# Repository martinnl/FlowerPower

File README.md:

FlowerPower
===========

Flower watering and nutrition controller
as

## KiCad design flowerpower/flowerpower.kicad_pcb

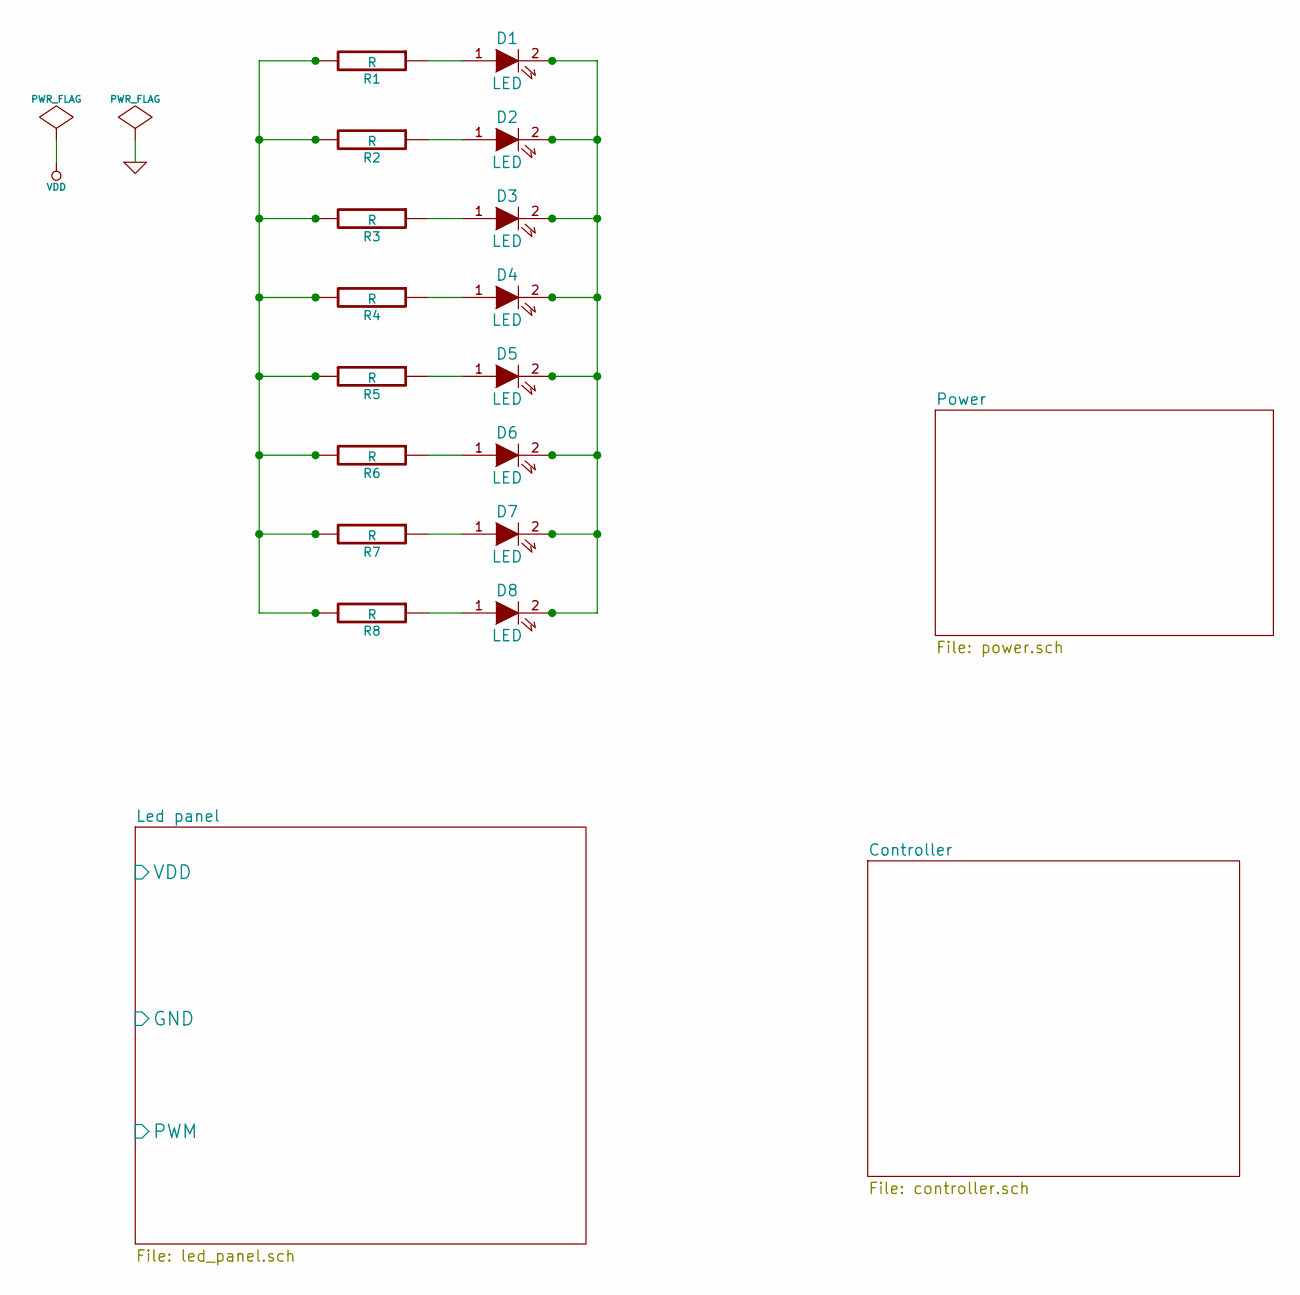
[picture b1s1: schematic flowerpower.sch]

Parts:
D1, D2, D3, D4, D5, D6, D7, D8: LED
R1, R2, R3, R4, R5, R6, R7, R8: R

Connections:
unnamed: D6.1 (A), R6.1
unnamed: D5.1 (A), R5.1
unnamed: D7.1 (A), R7.1
unnamed: D4.1 (A), R4.1
unnamed: D3.1 (A), R3.1
unnamed: R1.2, R2.2, R3.2, R4.2, R5.2, R6.2, R7.2, R8.2
unnamed: D1.2 (K), D2.2 (K), D3.2 (K), D4.2 (K), D5.2 (K), D6.2 (K), D7.2 (K), D8.2 (K)
unnamed: D8.1 (A), R8.1
unnamed: D1.1 (A), R1.1
unnamed: D2.1 (A), R2.1

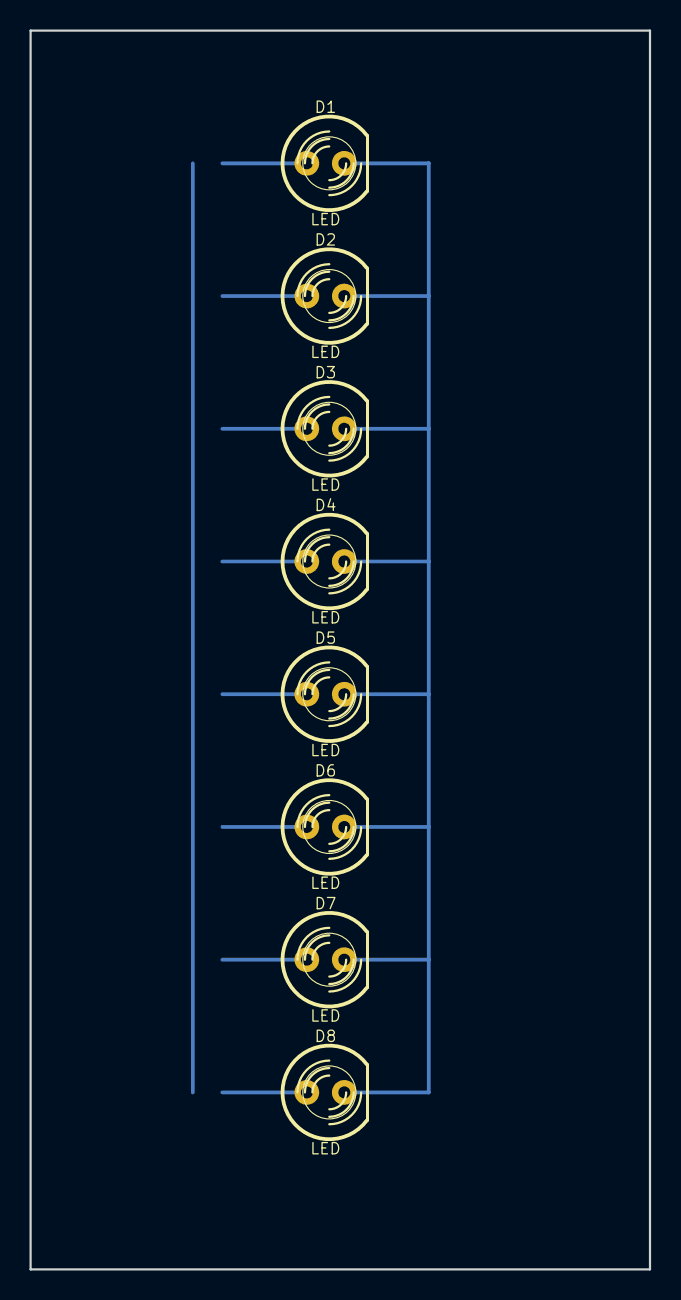
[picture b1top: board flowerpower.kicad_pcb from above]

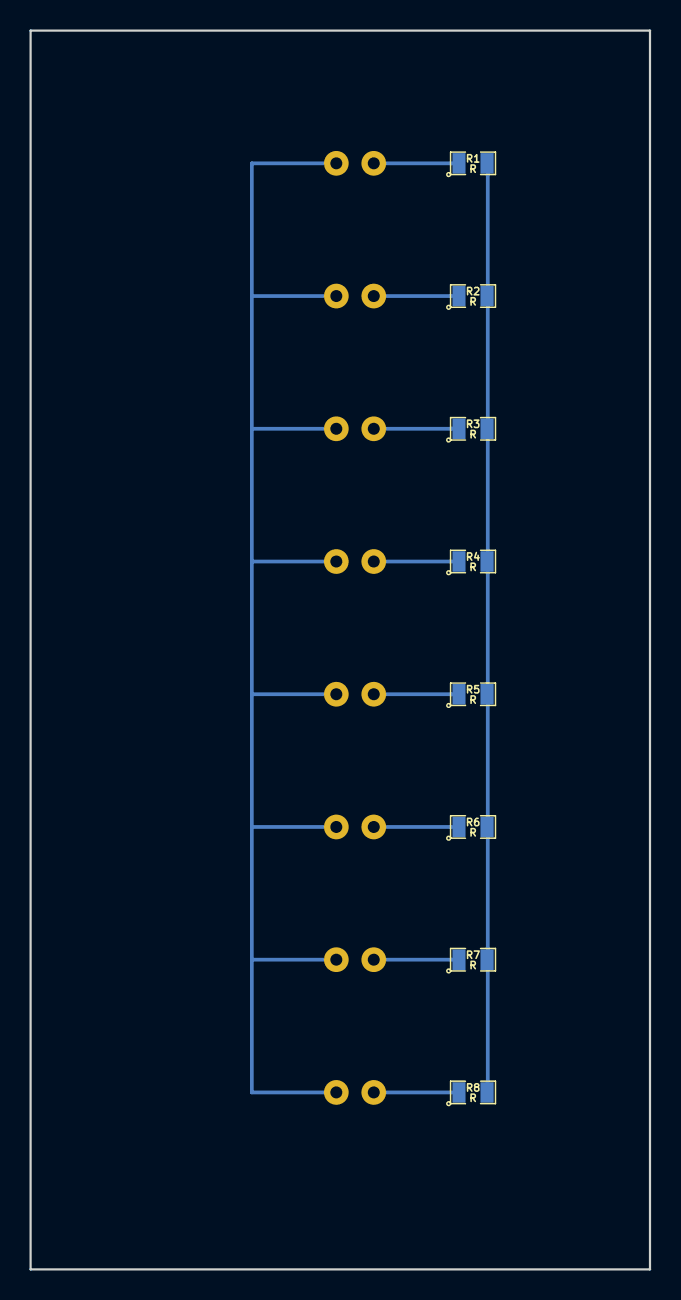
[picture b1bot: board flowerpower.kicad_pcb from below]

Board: 2 copper layers, 42.0 x 84.0 mm, 16 parts (8 on the bottom side), 10 nets.

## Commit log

2013-10-18 Andringar
2013-10-18 TESTAR LITE
    vafan
